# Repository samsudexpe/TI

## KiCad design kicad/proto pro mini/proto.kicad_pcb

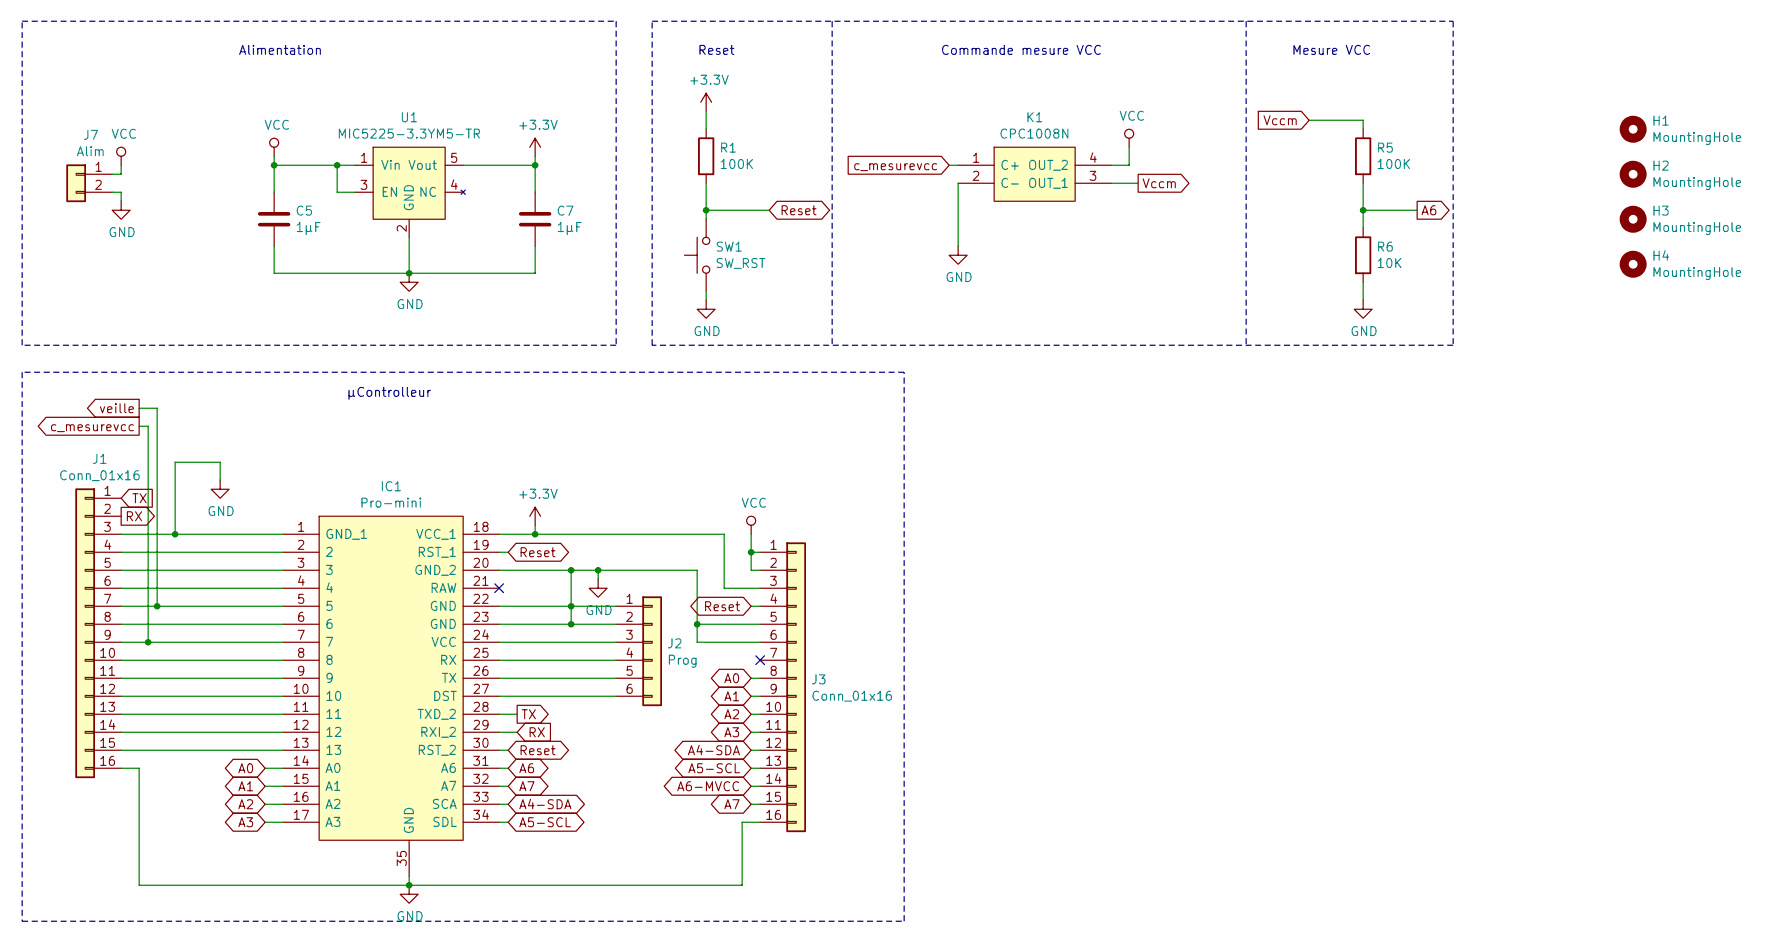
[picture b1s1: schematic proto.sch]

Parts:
C5, C7: 1µF; C_0603_1608Metric
H1, H2, H3, H4: MountingHole; MountingHole_3.5mmmodif
IC1: Pro-mini; DEV11114; Manufacturer_Part_Number DEV-11114; Mouser Part Number 474-DEV-11114
J1, J3: Conn_01x16; PinHeader_1x16_P2.54mm_Vertical
J2: Prog; PinHeader_1x06_P2.54mm_Vertical
J7: Alim; PinHeader_1x02_P2.54mm_Vertical
K1: CPC1008N; SOP254P610X216-4N; Manufacturer_Part_Number CPC1008N; Mouser Part Number 849-CPC1008N
R1, R5: 100K; R_0603_1608Metric
R6: 10K; R_0603_1608Metric
SW1: SW_RST; SW_PUSH_6mm
U1: MIC5225-3.3YM5-TR; SOT-23-5

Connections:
+3V3: C7.1, IC1.18 (VCC_1), J3.3, R1.1, U1.5 (Vout)
A0: IC1.14 (A0), J3.8
A1: IC1.15 (A1), J3.9
A2: IC1.16 (A2), J3.10
A3: IC1.17 (A3), J3.11
A4-SDA: IC1.33 (SCA), J3.12
A5-SCL: IC1.34 (SDL), J3.13
A6: IC1.31 (A6), R5.2, R6.1
A7: IC1.32 (A7), J3.15
GND: C5.2, C7.2, IC1.1 (GND_1), IC1.20 (GND_2), IC1.22 (GND), IC1.23 (GND), IC1.35 (GND), J1.3, J1.16, J2.1, J2.2, J3.5, J3.6, J3.16, J7.2, K1.2 (C-), R6.2, SW1.1, U1.2 (GND)
unnamed: IC1.2, J1.4
unnamed: IC1.3, J1.5
unnamed: IC1.4, J1.6
unnamed: IC1.6, J1.8
unnamed: IC1.8, J1.10
unnamed: IC1.9, J1.11
unnamed: IC1.10, J1.12
unnamed: IC1.11, J1.13
unnamed: IC1.12, J1.14
unnamed: IC1.13, J1.15
unnamed: IC1.24 (VCC), J2.3
unnamed: IC1.25 (RX), J2.4
unnamed: IC1.26 (TX), J2.5
unnamed: IC1.27 (DST), J2.6
RX: IC1.29 (RXI_2), J1.2
Reset: IC1.19 (RST_1), IC1.30 (RST_2), J3.4, R1.2, SW1.2
TX: IC1.28 (TXD_2), J1.1
VCC: C5.1, J3.1, J3.2, J7.1, K1.4 (OUT_2), U1.1 (Vin), U1.3 (EN)
Vccm: K1.3 (OUT_1), R5.1
c_mesurevcc: IC1.7, J1.9, K1.1 (C+)
veille: IC1.5, J1.7

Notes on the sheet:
Mesure VCC
Commande mesure VCC
Reset
Alimentation
µControlleur

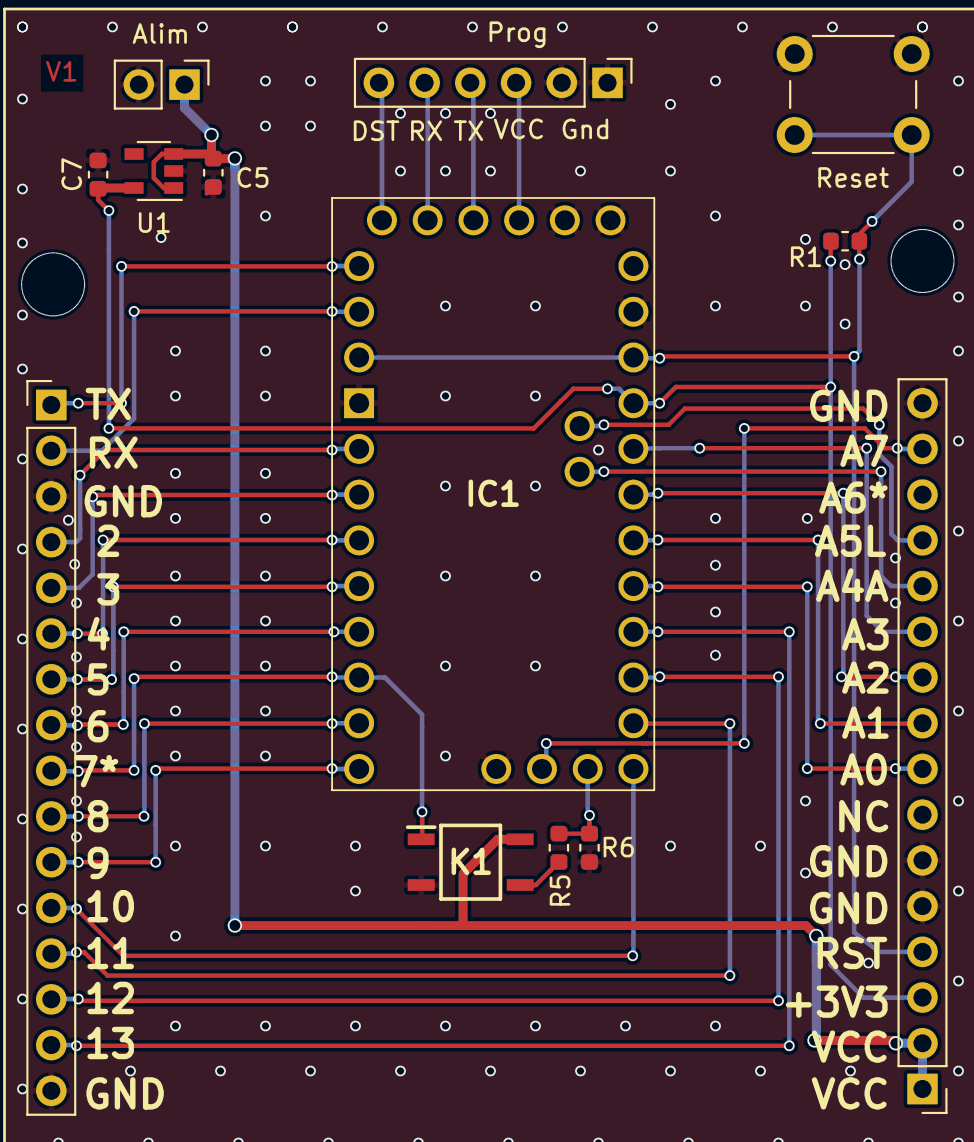
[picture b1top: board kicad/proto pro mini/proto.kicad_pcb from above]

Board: 2 copper layers, 17 parts (0 on the bottom side), 31 nets.

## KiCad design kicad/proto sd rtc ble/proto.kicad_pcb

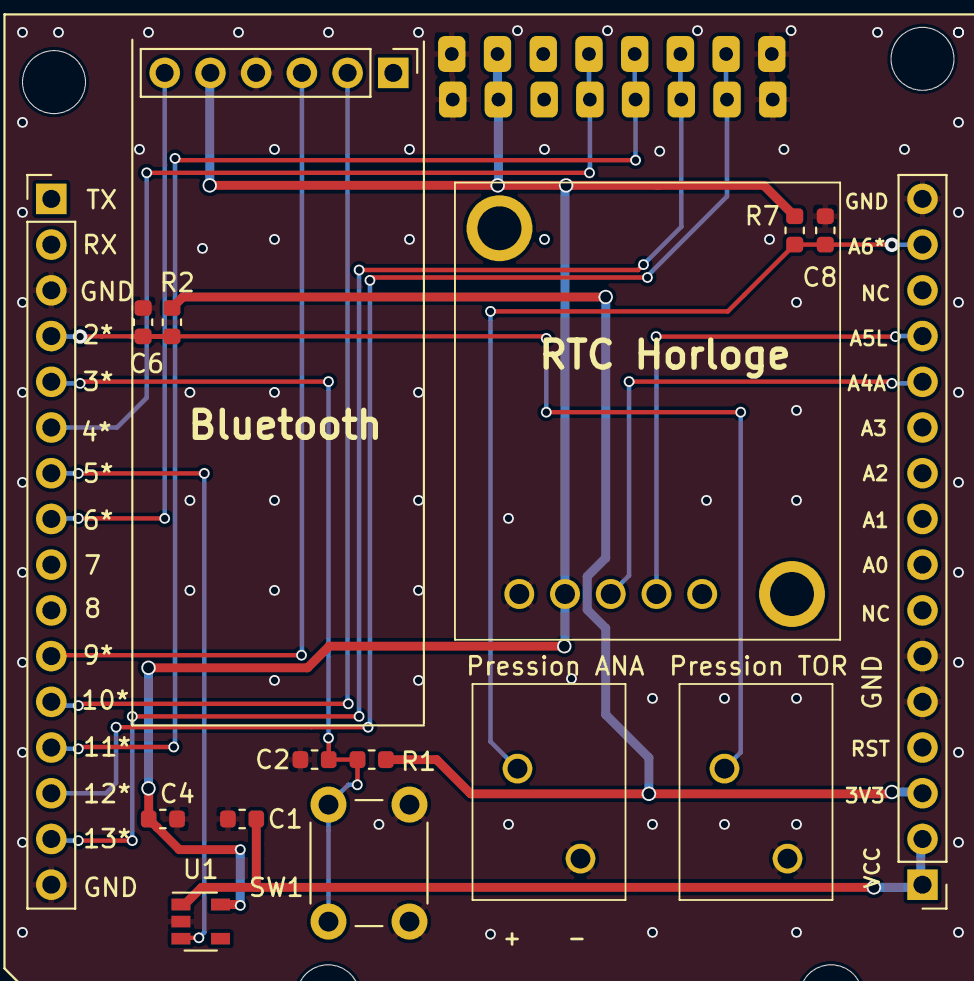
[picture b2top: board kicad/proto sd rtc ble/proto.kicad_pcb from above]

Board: 2 copper layers, 21 parts (1 on the bottom side), 17 nets.

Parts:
C1, C4: 1µF; C_0603_1608Metric
C2, C6, C8: 0.1µF; C_0603_1608Metric
H1, H2, H3, H4: MountingHole; MountingHole_3.5mmmodif
J1, J3: Conn_01x16; PinHeader_1x16_P2.54mm_Vertical
J2: SD; carte_sd
J4: ble; PinHeader_1x06_P2.54mm_Vertical
J6: RTC; ADA3295
J8: CapTOR; 250202
J9: CapAna; 250202
R1, R2: 100K; R_0603_1608Metric
R7: 10K; R_0603_1608Metric
SW1: SW_ble; SW_PUSH_6mm
U1: NCP718BSN330T1G; SOT-23-5

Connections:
+3.3V_Mini: J3.3, R1.1, R2.1
+3V3: C4.1, J2.2, J2.10, J4.5, J6.2, R7.1, U1.5
A7: C8.1, J3.15, J9.1, R7.2
CS: J1.6, J2.4, J2.12
CapTOR: C6.1, J1.4, J8.1, R2.2
EN_ble: J1.8, J4.6
GND: C1.2, C2.2, C4.2, C6.2, C8.2, J1.3, J1.16, J2.1, J2.8, J2.9, J2.16, J3.5, J3.6, J3.16, J4.4, J6.1, J8.2, J9.2, SW1.1, U1.2
MISO: J1.14, J2.7, J2.15
MOSI: J1.13, J2.5, J2.13
RTC_SCA: J3.12, J6.3
RTC_SDL: J3.13, J6.4
RX_ble: J1.11, J4.3
SCK: J1.15, J2.6, J2.14
TX_ble: J1.12, J4.2
VCC: C1.1, J3.1, J3.2, U1.1
veille: J1.7, U1.3
wakeblue: C2.1, J1.5, R1.2, SW1.2
